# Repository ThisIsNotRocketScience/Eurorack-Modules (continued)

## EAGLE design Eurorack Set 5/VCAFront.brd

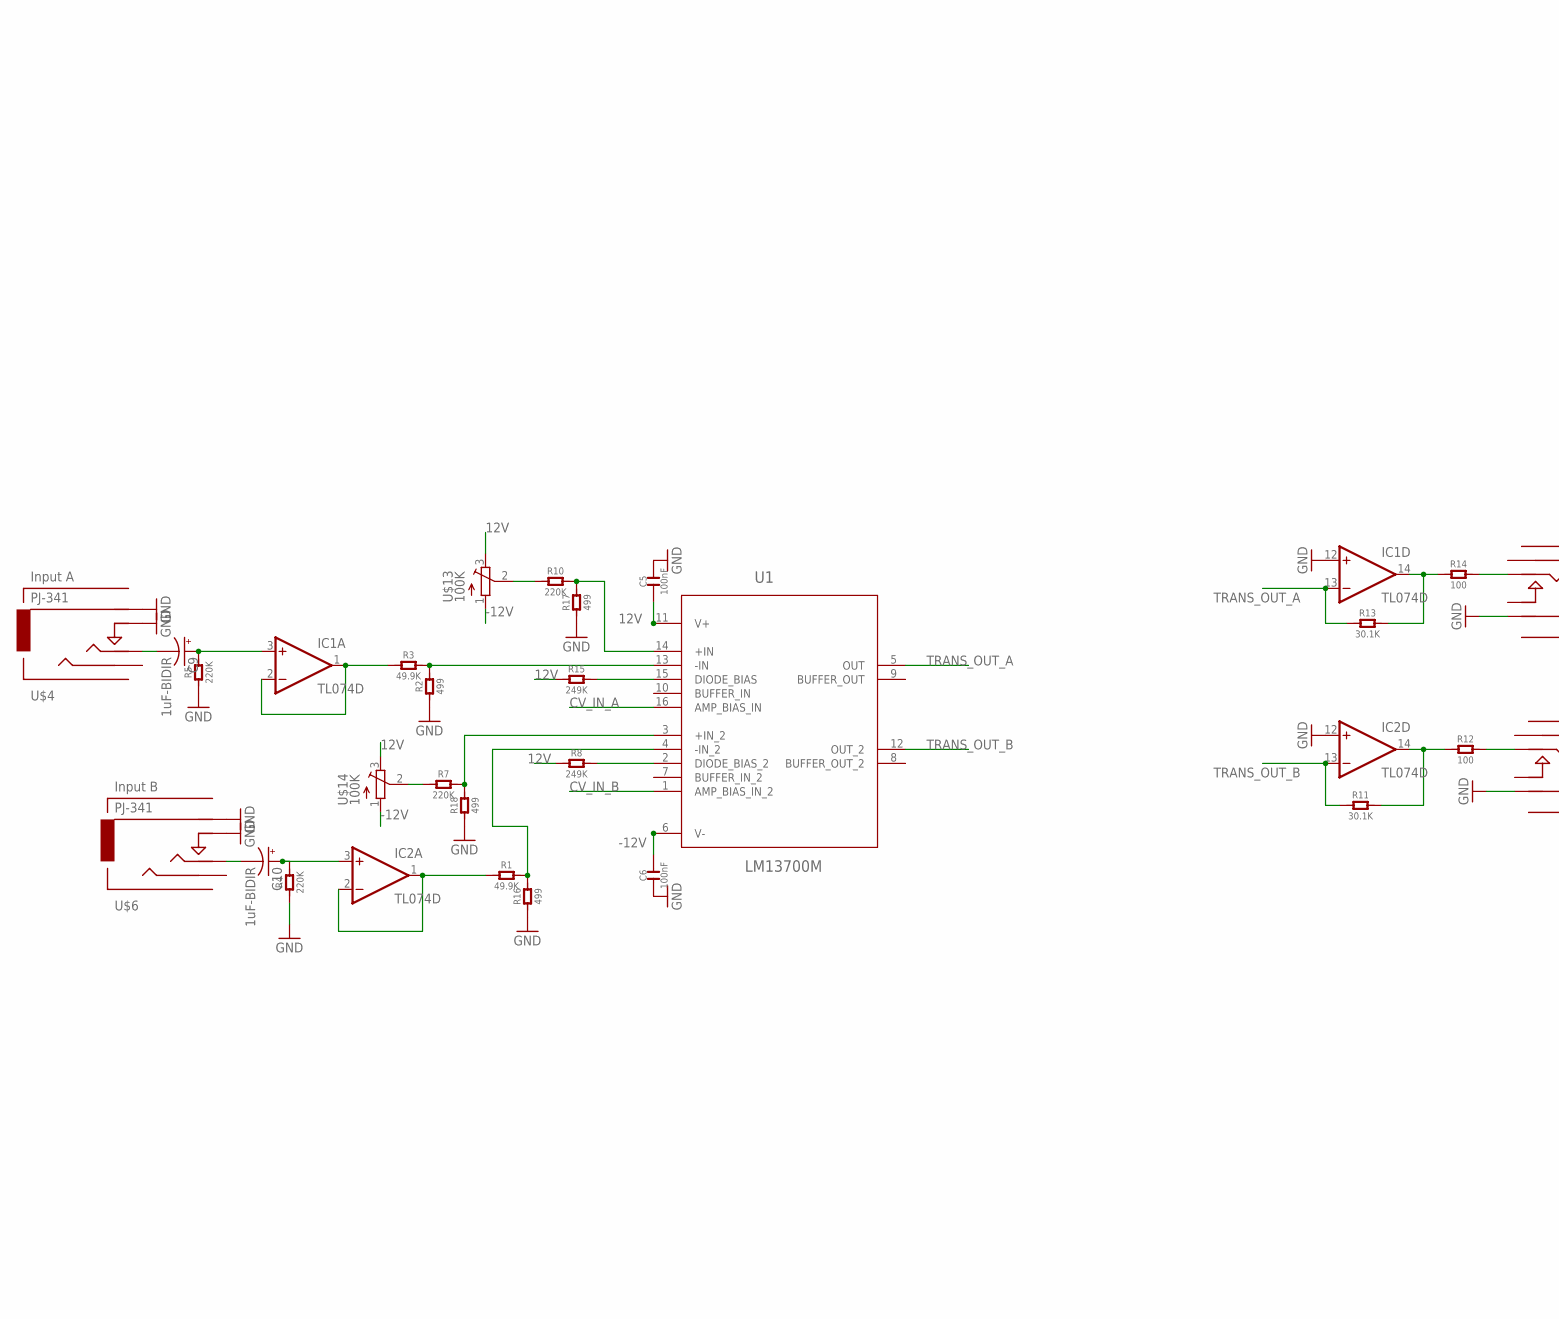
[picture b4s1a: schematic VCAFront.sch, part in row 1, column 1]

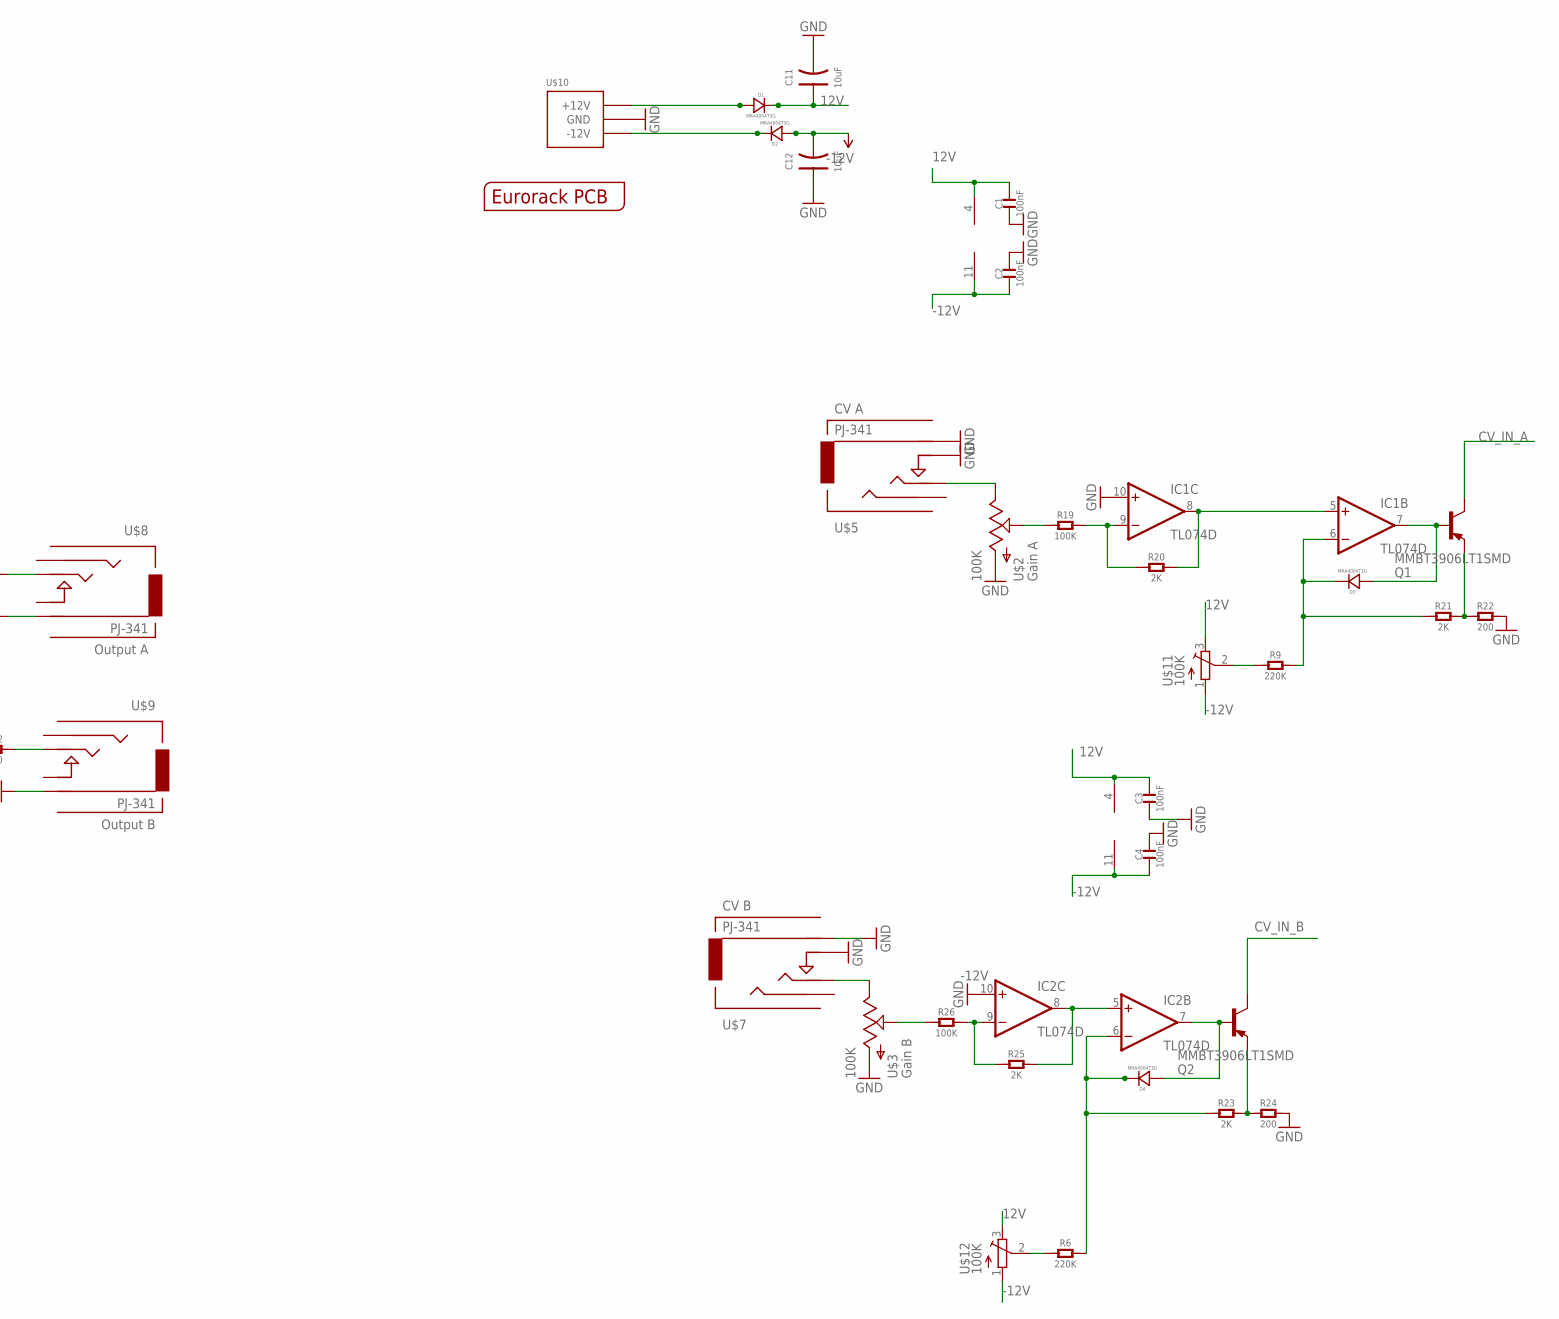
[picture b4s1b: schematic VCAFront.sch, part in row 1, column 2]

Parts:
C1, C2, C3, C4, C5, C6: 100nF; C0603
C9, C10: 1uF-BIDIR; 153CLV-0505
C11, C12: 10uF; AVX-A
D1, D2, D3, D4: MRA4004T3G; DO-214AC; MPN US1G-E3/5AT
IC1, IC2: TL074D; SO14
Q1, Q2: MMBT3906LT1SMD; SOT23-BEC
R1, R3: 49.9K; C0805
R2, R16, R17, R18: 499; C0805
R4, R5, R6, R7, R9, R10: 220K; C0805
R8, R15: 249K; C0805
R11, R13: 30.1K; C0805
R12, R14: 100; C0805
R19, R26: 100K; C0805
R20, R21, R23, R25: 2K; C0805
R22, R24: 200; C0805
U1: LM13700M; SOIC127P620X175-16N
U$1: EURORACK_PCB4HP; EURORACK4HPPCB
U$2, U$3: 100K; OG-POTS_ALPS_POT_VERTICAL
U$4, U$5, U$6, U$7: PJ-341; 3.5MM-JACK-SWITCH-13MM-INPUT
U$8, U$9: PJ-341; 3.5MM-JACK-SWITCH-13MM-OUTPUT
U$10: POWER_SIMPLE10; POWER_10
U$11, U$12, U$13, U$14: 100K; TC33X

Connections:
12V: C1.2, C3.2, C5.1, C11.+ (1), D1.2 (-), IC1.4 (V+), IC2.4 (V+), R8.1, R15.1, U1.11 (V+), U$11.3 (E), U$12.3 (E), U$13.3 (E), U$14.3 (E)
-12V: C2.1, C4.1, C6.2, C12.- (2), D2.1 (+), IC1.11 (V-), IC2.11 (V-), U1.6 (V-), U$11.1 (A), U$12.1 (A), U$13.1 (A), U$14.1 (A)
CV_IN_A: Q1.C, U1.16 (AMP_BIAS_IN)
CV_IN_B: Q2.C, U1.1 (AMP_BIAS_IN_2)
GND: C1.1, C2.2, C3.1, C4.2, C5.2, C6.1, C11.- (2), C12.+ (1), IC1.10 (+IN), IC1.12 (+IN), IC2.10 (+IN), IC2.12 (+IN), R2.1, R4.1, R5.1, R16.1, R17.1, R18.1, R22.2, R24.2, U$2.P$3 (A), U$3.P$3 (A), U$4.RING@3 (RING), U$4.SWITCH@3 (SWITCH), U$5.RING@3 (RING), U$5.SWITCH@3 (SWITCH), U$6.RING@3 (RING), U$6.SWITCH@3 (SWITCH), U$7.RING@3 (RING), U$7.SWITCH@3 (SWITCH), U$8.RING@3 (RING), U$9.RING@3 (RING), U$10.3 (GND), U$10.4 (GND), U$10.5 (GND), U$10.6 (GND), U$10.7 (GND), U$10.8 (GND)
unnamed: R14.2, U$8.TIP@3 (TIP)
unnamed: IC1.14 (OUT), R13.2, R14.1
unnamed: R8.2, U1.2 (DIODE_BIAS_2)
unnamed: R15.2, U1.15 (DIODE_BIAS)
unnamed: R12.2, U$9.TIP@3 (TIP)
unnamed: IC2.14 (OUT), R11.2, R12.1
unnamed: R19.1, U$2.P$2 (S)
unnamed: R10.1, U$13.2 (S)
unnamed: R9.1, U$11.2 (S)
unnamed: R7.1, U$14.2 (S)
unnamed: R6.1, U$12.2 (S)
unnamed: C9.-, U$4.TIP@3 (TIP)
unnamed: C10.-, U$6.TIP@3 (TIP)
unnamed: C9.+, IC1.3 (+IN), R5.2
unnamed: C10.+, IC2.3 (+IN), R4.2
unnamed: IC1.1 (OUT), IC1.2 (-IN), R3.1
unnamed: IC2.1 (OUT), IC2.2 (-IN), R1.1
unnamed: R2.2, R3.2, U1.13 (-IN)
unnamed: R1.2, R16.2, U1.4 (-IN_2)
unnamed: R10.2, R17.2, U1.14 (+IN)
unnamed: U$3.P$1 (E), U$7.TIP@3 (TIP)
unnamed: R7.2, R18.2, U1.3 (+IN_2)
unnamed: U$2.P$1 (E), U$5.TIP@3 (TIP)
unnamed: IC1.9 (-IN), R19.2, R20.1
unnamed: IC1.5 (+IN), IC1.8 (OUT), R20.2
unnamed: D3.2 (-), IC1.6 (-IN), R9.2, R21.1
unnamed: D1.1 (+), U$10.9 (+12V), U$10.10 (+12V)
unnamed: D3.1 (+), IC1.7 (OUT), Q1.B
unnamed: Q1.E, R21.2, R22.1
unnamed: D4.2 (-), IC2.6 (-IN), R6.2, R23.1
unnamed: D4.1 (+), IC2.7 (OUT), Q2.B
unnamed: Q2.E, R23.2, R24.1
unnamed: IC2.5 (+IN), IC2.8 (OUT), R25.2
unnamed: R26.1, U$3.P$2 (S)
unnamed: IC2.9 (-IN), R25.1, R26.2
unnamed: D2.2 (-), U$10.1 (-12V), U$10.2 (-12V)
TRANS_OUT_A: IC1.13 (-IN), R13.1, U1.5 (OUT)
TRANS_OUT_B: IC2.13 (-IN), R11.1, U1.12 (OUT_2)

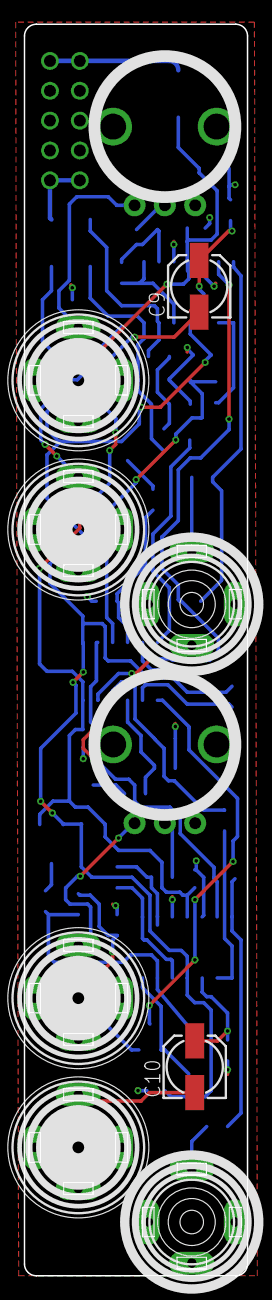
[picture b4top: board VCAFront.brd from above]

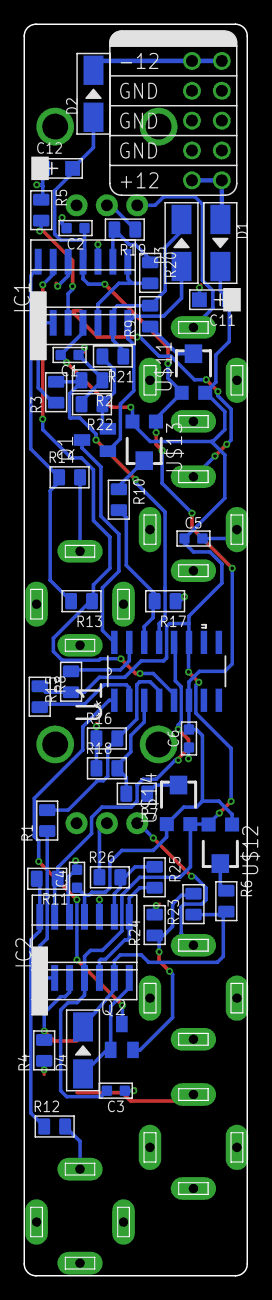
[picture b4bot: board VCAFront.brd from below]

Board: 2 copper layers, 19.0 x 106.5 mm, 59 parts (48 on the bottom side), 43 nets.

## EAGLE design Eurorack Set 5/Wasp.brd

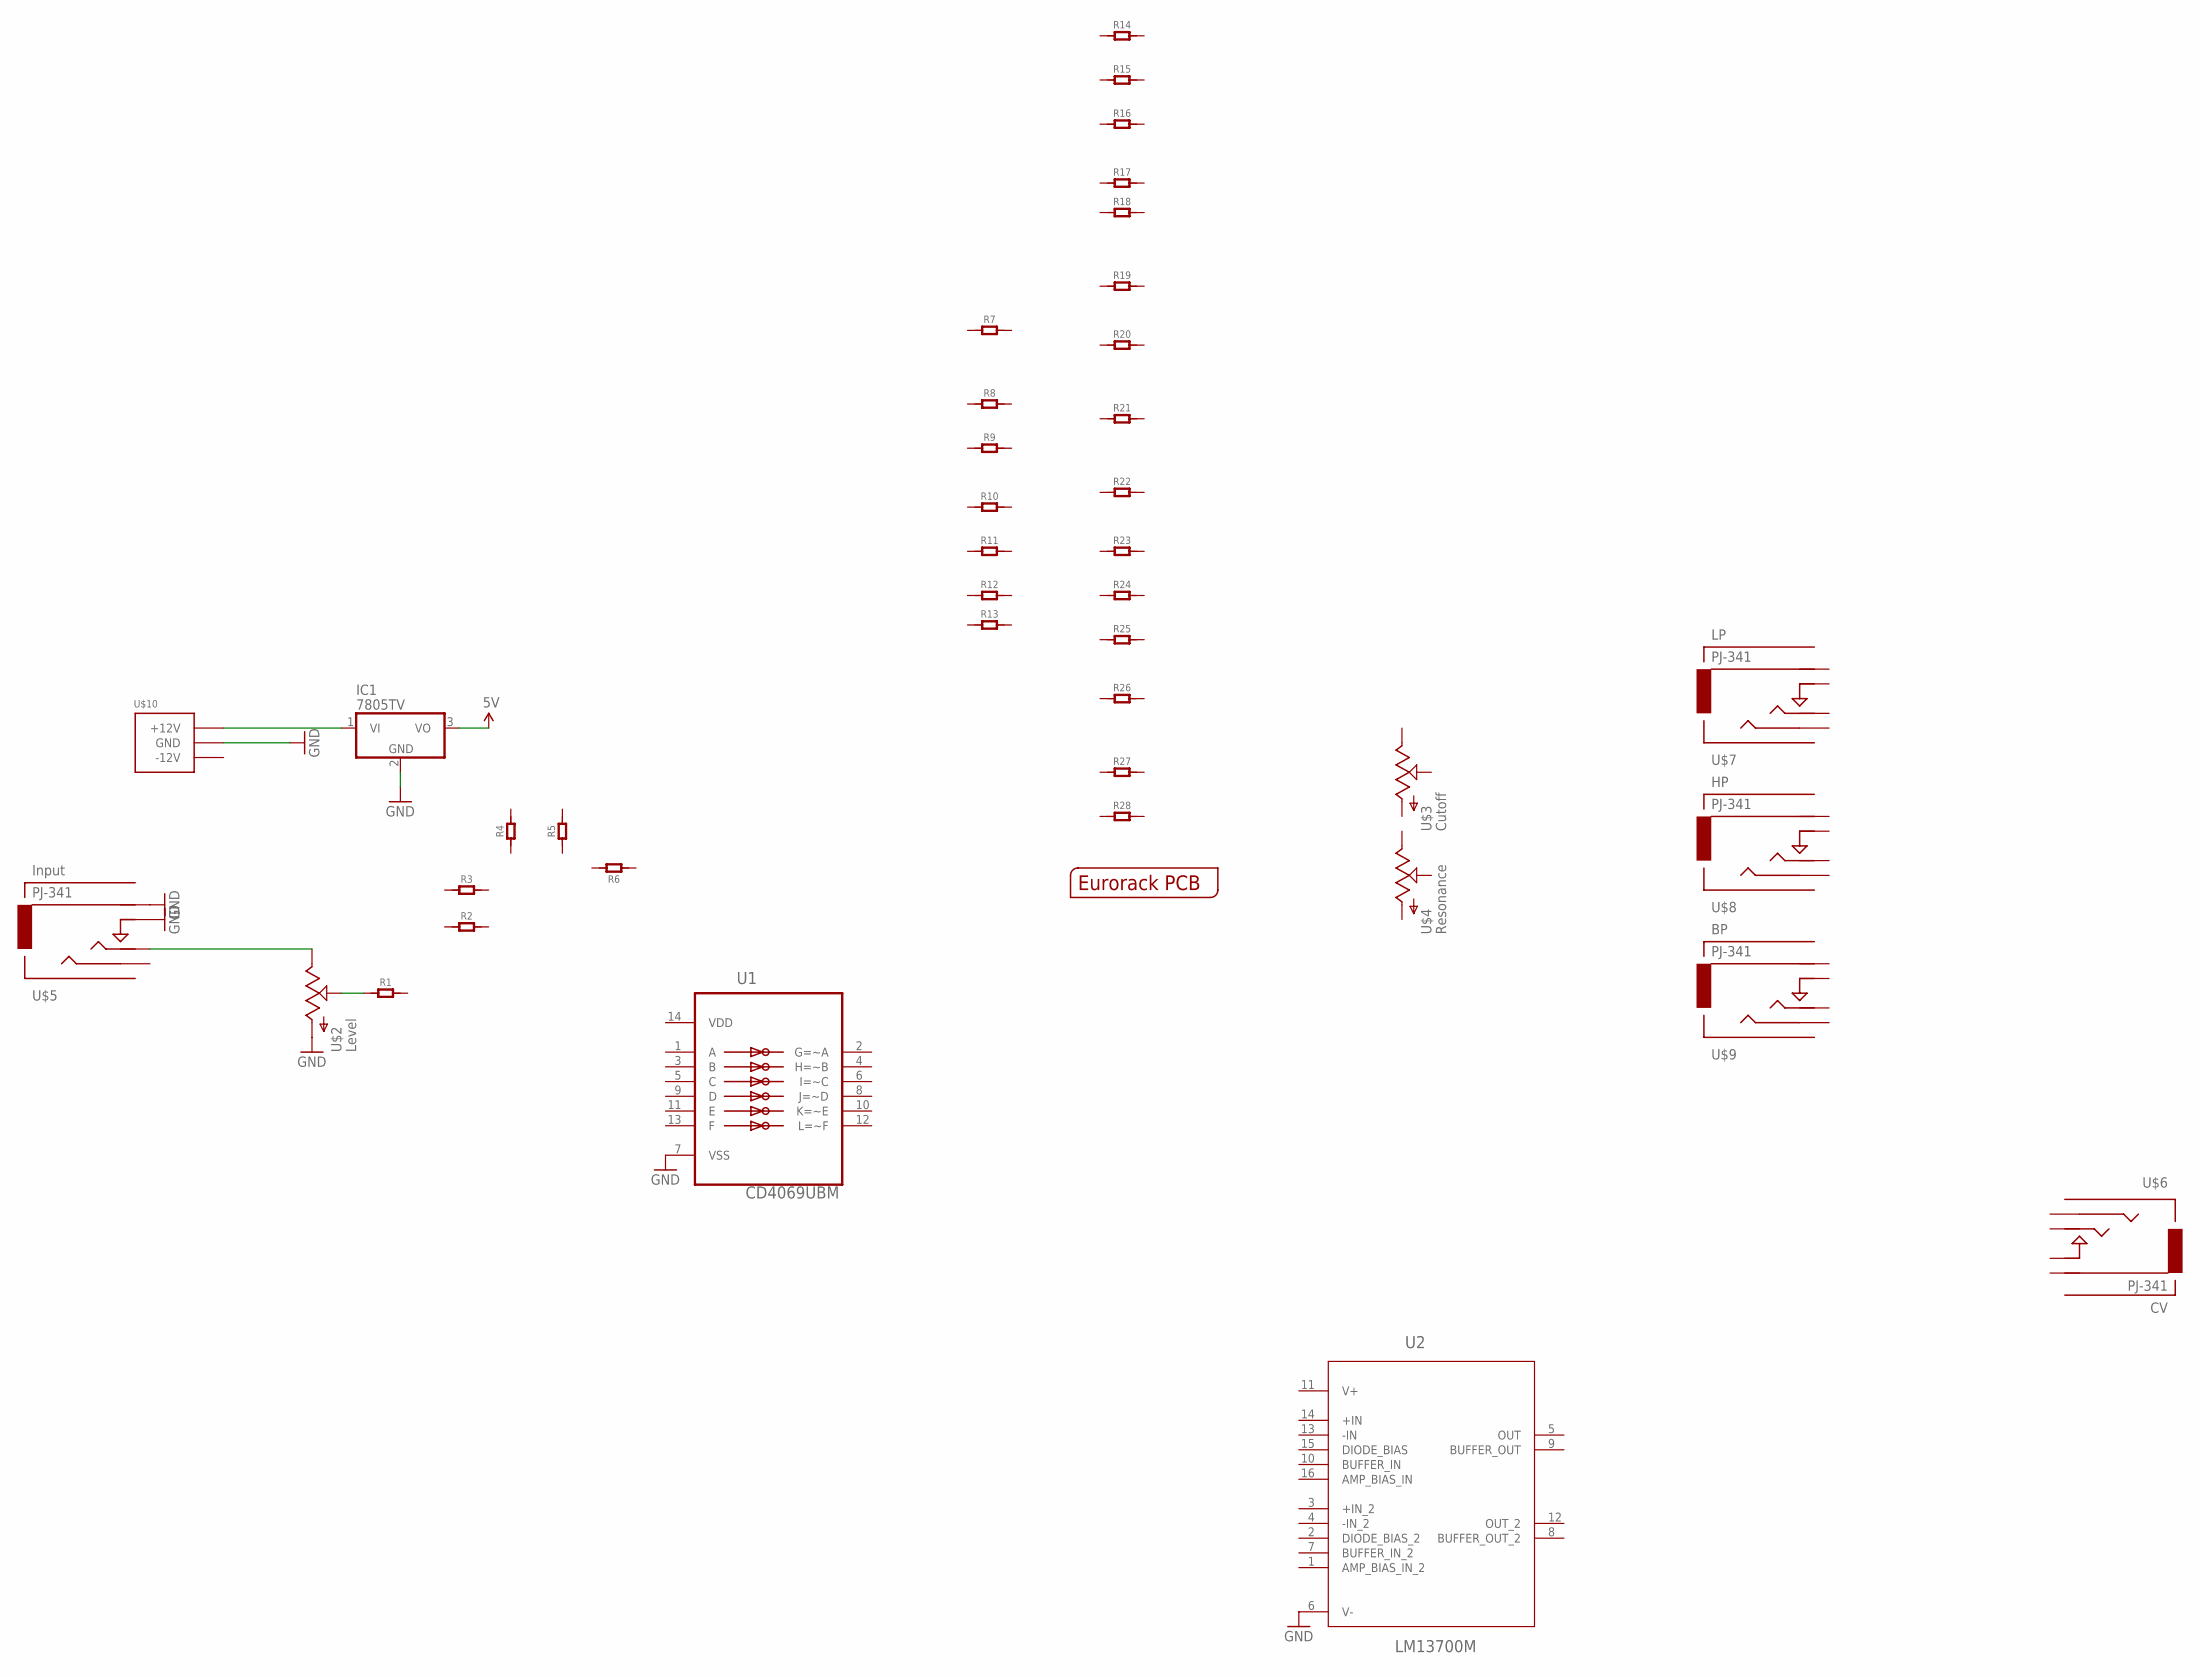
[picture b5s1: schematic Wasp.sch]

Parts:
IC1: 7805TV; TO220V
R1, R2, R3, R4, R5, R6, R7, R8, R9, R10, R11, R12, R13, R14, R15, R16, R17, R18, R19, R20, R21, R22, R23, R24, R25, R26, R27, R28: R-0603; R0603
U1: CD4069UBM; SOIC127P600X175-14N
U2: LM13700M; SOIC127P620X175-16N
U$1: EURORACK_PCB4HP; EURORACK4HPPCB
U$2, U$3, U$4: POTZEPHPOT; OG-POTS_ALPS_POT_VERTICAL
U$5, U$6: PJ-341; 3.5MM-JACK-SWITCH-13MM-INPUT
U$7, U$8, U$9: PJ-341; 3.5MM-JACK-SWITCH-13MM-OUTPUT
U$10: POWER_SIMPLE10; POWER_10

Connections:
5V: IC1.3 (VO)
GND: IC1.2 (GND), U1.7 (VSS), U2.6 (V-), U$2.P$3 (A), U$5.RING@3 (RING), U$5.SWITCH@3 (SWITCH), U$10.3 (GND), U$10.4 (GND), U$10.5 (GND), U$10.6 (GND), U$10.7 (GND), U$10.8 (GND)
unnamed: R1.1, U$2.P$2 (S)
unnamed: U$2.P$1 (E), U$5.TIP@3 (TIP)
unnamed: IC1.1 (VI), U$10.9 (+12V), U$10.10 (+12V)
V+: U2.11 (V+)
VDD: U1.14 (VDD)

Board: 2 copper layers, 41 parts (1 on the bottom side), 4 nets, no tracks yet.
